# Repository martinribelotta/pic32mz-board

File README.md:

pic32mz-board
=============

PIC32MZ development board for 144 pin QFP packages

[Schematic in PDF](docs/mz.pdf)

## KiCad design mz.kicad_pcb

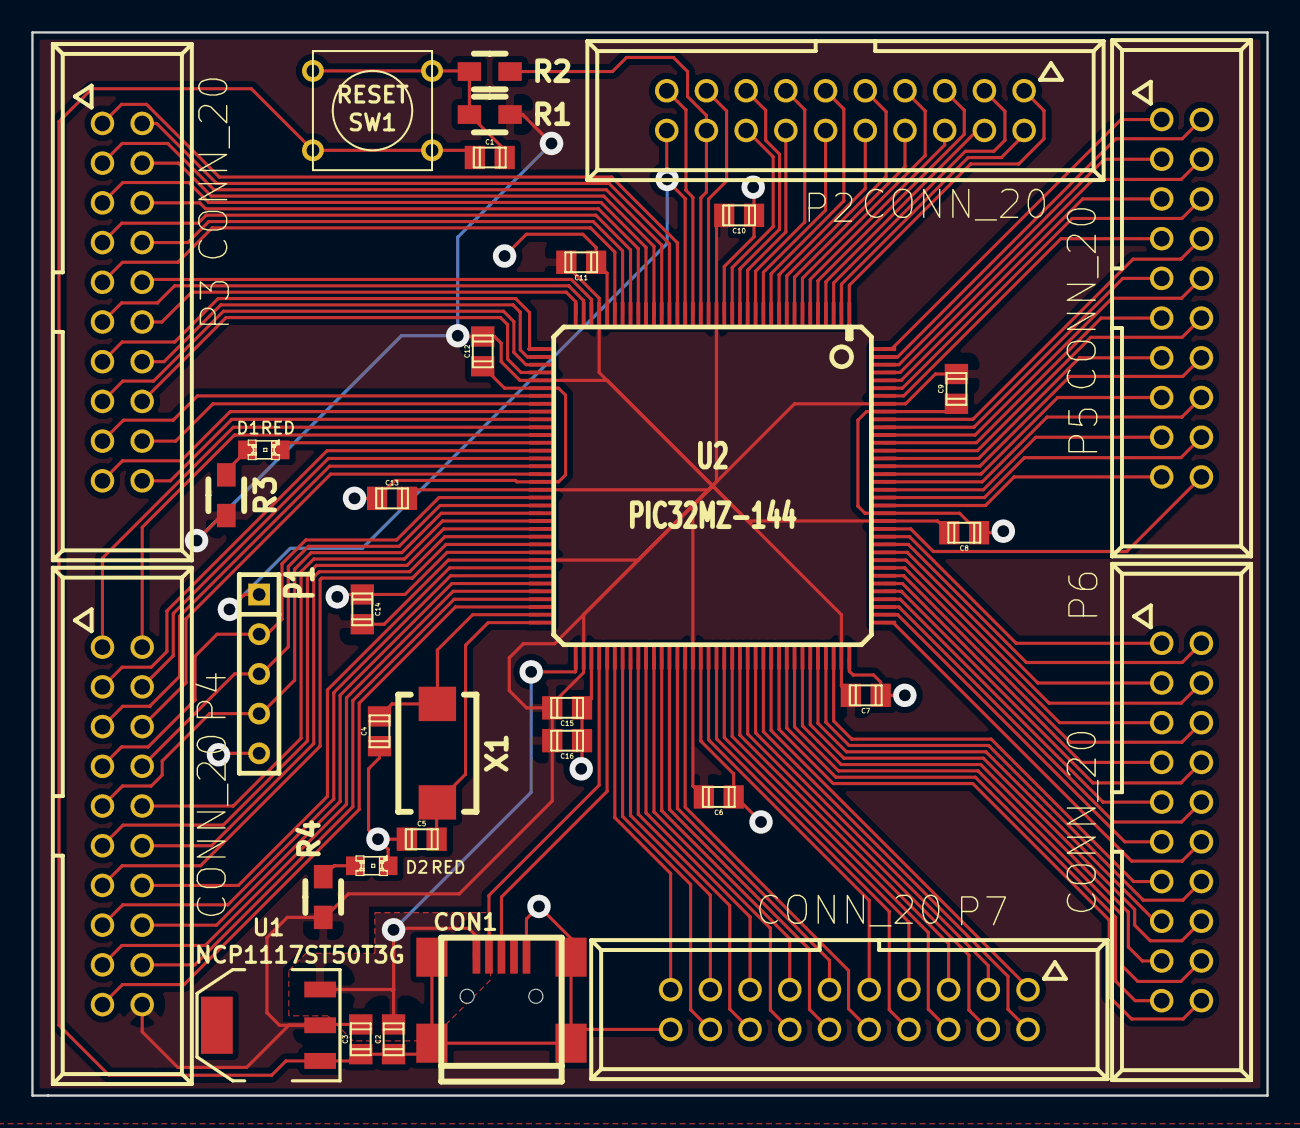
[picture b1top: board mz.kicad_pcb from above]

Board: 2 copper layers, 79.0 x 68.0 mm, 34 parts (0 on the bottom side), 129 nets.

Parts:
C1, C15: 1u; c_0805
C2, C3: 10u; c_0805
C4, C5: 10p; c_0805
C6, C7, C8, C9, C10, C11, C12, C13, C14, C16: 100n; c_0805
CON1: USB-MINI-B; USB_MINI_B
D1, D2: RED; LED-0805
P1: JTAG; SIL-5
P2, P3, P4, P5, P6, P7: CONN_20; VASCH10x2
R1: 10k; Resistor_SMD0805_HandSoldering
R2, R3, R4: 220R; Resistor_SMD0805_HandSoldering
SW1: RESET; SW_PUSH_SMALL
U1: NCP1117ST50T3G; SOT223
U2: PIC32MZ-144; TQFP144
X1: 24MHz; Crystal_FOX-FE_SMD

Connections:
+3.3V: C3.1, C6.1, C7.1, C8.1, C9.1, C10.1, C11.1, C12.1, C13.1, C14.1, C15.1, C16.1, P4.20, R1.1, R3.2, R4.2, U1.2, U2.18, U2.33, U2.41, U2.55, U2.64, U2.74, U2.88, U2.107, U2.122, U2.137
/D+: CON1.3, U2.77
/D-: CON1.2, U2.76
/JTAG_TCK: P1.2, P4.7, U2.56
/JTAG_TDI: P1.3, P4.8, U2.57
/JTAG_TDO: P1.4, P4.9, U2.58
/JTAG_TMS: P1.1, P2.20, U2.22
/LED_GPIO: D1.2, U2.49
/MCLR: P2.18, R2.1, U2.20
/VBUS: C2.1, CON1.1, U1.3, U2.73
GND: C1.2, C2.2, C3.2, C4.2, C5.2, C6.2, C7.2, C8.2, C9.2, C10.2, C11.2, C12.2, C13.2, C14.2, C15.2, C16.2, CON1.5, CON1.6, CON1.7, CON1.8, CON1.9, D2.2, P1.5, P7.20, SW1.1, U1.1, U2.17, U2.32, U2.42, U2.54, U2.63, U2.75, U2.89, U2.108, U2.123, U2.136
unnamed: C1.1, R1.2, R2.2, SW1.2
unnamed: C4.1, U2.71, X1.1
unnamed: C5.1, U2.72, X1.2
unnamed: D1.1, R3.1
unnamed: D2.1, R4.1
unnamed: P2.1, U2.1
unnamed: P2.2, U2.2
unnamed: P2.3, U2.3
unnamed: P2.4, U2.4
unnamed: P2.5, U2.5
unnamed: P2.6, U2.6
unnamed: P2.7, U2.7
unnamed: P2.8, U2.8
unnamed: P2.9, U2.9
unnamed: P2.10, U2.10
unnamed: P2.11, U2.11
unnamed: P2.12, U2.12
unnamed: P2.13, U2.13
unnamed: P2.14, U2.14
unnamed: P2.15, U2.15
unnamed: P2.16, U2.16
unnamed: P2.17, U2.19
unnamed: P2.19, U2.21
unnamed: P3.1, U2.23
unnamed: P3.2, U2.24
unnamed: P3.3, U2.25
unnamed: P3.4, U2.26
unnamed: P3.5, U2.27
unnamed: P3.6, U2.28
unnamed: P3.7, U2.29
unnamed: P3.8, U2.30
unnamed: P3.9, U2.31
unnamed: P3.10, U2.34
unnamed: P3.11, U2.35
unnamed: P3.12, U2.36
unnamed: P3.13, U2.37
unnamed: P3.14, U2.38
unnamed: P3.15, U2.39
unnamed: P3.16, U2.40
unnamed: P3.17, U2.43
unnamed: P3.18, U2.44
unnamed: P3.19, U2.45
unnamed: P3.20, U2.46
unnamed: P4.1, U2.47
unnamed: P4.2, U2.48
unnamed: P4.3, U2.50
unnamed: P4.4, U2.51
unnamed: P4.5, U2.52
unnamed: P4.6, U2.53
unnamed: P4.10, U2.59
unnamed: P4.11, U2.60
unnamed: P4.12, U2.61
unnamed: P4.13, U2.62
unnamed: P4.14, U2.65
unnamed: P4.15, U2.66
unnamed: P4.16, U2.67
unnamed: P4.17, U2.68
unnamed: P4.18, U2.69
unnamed: P4.19, U2.70
unnamed: P5.1, U2.144
unnamed: P5.2, U2.143
unnamed: P5.3, U2.142
unnamed: P5.4, U2.141
unnamed: P5.5, U2.140
unnamed: P5.6, U2.139
unnamed: P5.7, U2.138
unnamed: P5.8, U2.135
unnamed: P5.9, U2.134
unnamed: P5.10, U2.133
unnamed: P5.11, U2.132
unnamed: P5.12, U2.131
unnamed: P5.13, U2.130
unnamed: P5.14, U2.129
unnamed: P5.15, U2.128
unnamed: P5.16, U2.127
unnamed: P5.17, U2.126
unnamed: P5.18, U2.125
unnamed: P5.19, U2.124
unnamed: P5.20, U2.121
unnamed: P6.1, U2.120
unnamed: P6.2, U2.119
unnamed: P6.3, U2.118
unnamed: P6.4, U2.117
unnamed: P6.5, U2.116
unnamed: P6.6, U2.115
unnamed: P6.7, U2.114
unnamed: P6.8, U2.113
unnamed: P6.9, U2.112
unnamed: P6.10, U2.111
unnamed: P6.11, U2.110
unnamed: P6.12, U2.109
unnamed: P6.13, U2.106
unnamed: P6.14, U2.105
unnamed: P6.15, U2.104
unnamed: P6.16, U2.103
unnamed: P6.17, U2.102
unnamed: P6.18, U2.101
unnamed: P6.19, U2.100
unnamed: P6.20, U2.99
unnamed: P7.1, U2.98
unnamed: P7.2, U2.97
unnamed: P7.3, U2.96
unnamed: P7.4, U2.95
unnamed: P7.5, U2.94
unnamed: P7.6, U2.93
unnamed: P7.7, U2.92
unnamed: P7.8, U2.91
unnamed: P7.9, U2.90
unnamed: P7.10, U2.87
unnamed: P7.11, U2.86
unnamed: P7.12, U2.85
unnamed: P7.13, U2.84
unnamed: P7.14, U2.83
unnamed: P7.15, U2.82
unnamed: P7.16, U2.81
unnamed: P7.17, U2.80
unnamed: P7.18, U2.79
unnamed: P7.19, U2.78

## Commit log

2014-12-28 Add contents
2014-12-28 Add preview image
2014-12-28 PDF schematics on docs/
2014-12-28 Added schematic
2014-12-30 Add power led
2014-12-30 Modify .gitignore
